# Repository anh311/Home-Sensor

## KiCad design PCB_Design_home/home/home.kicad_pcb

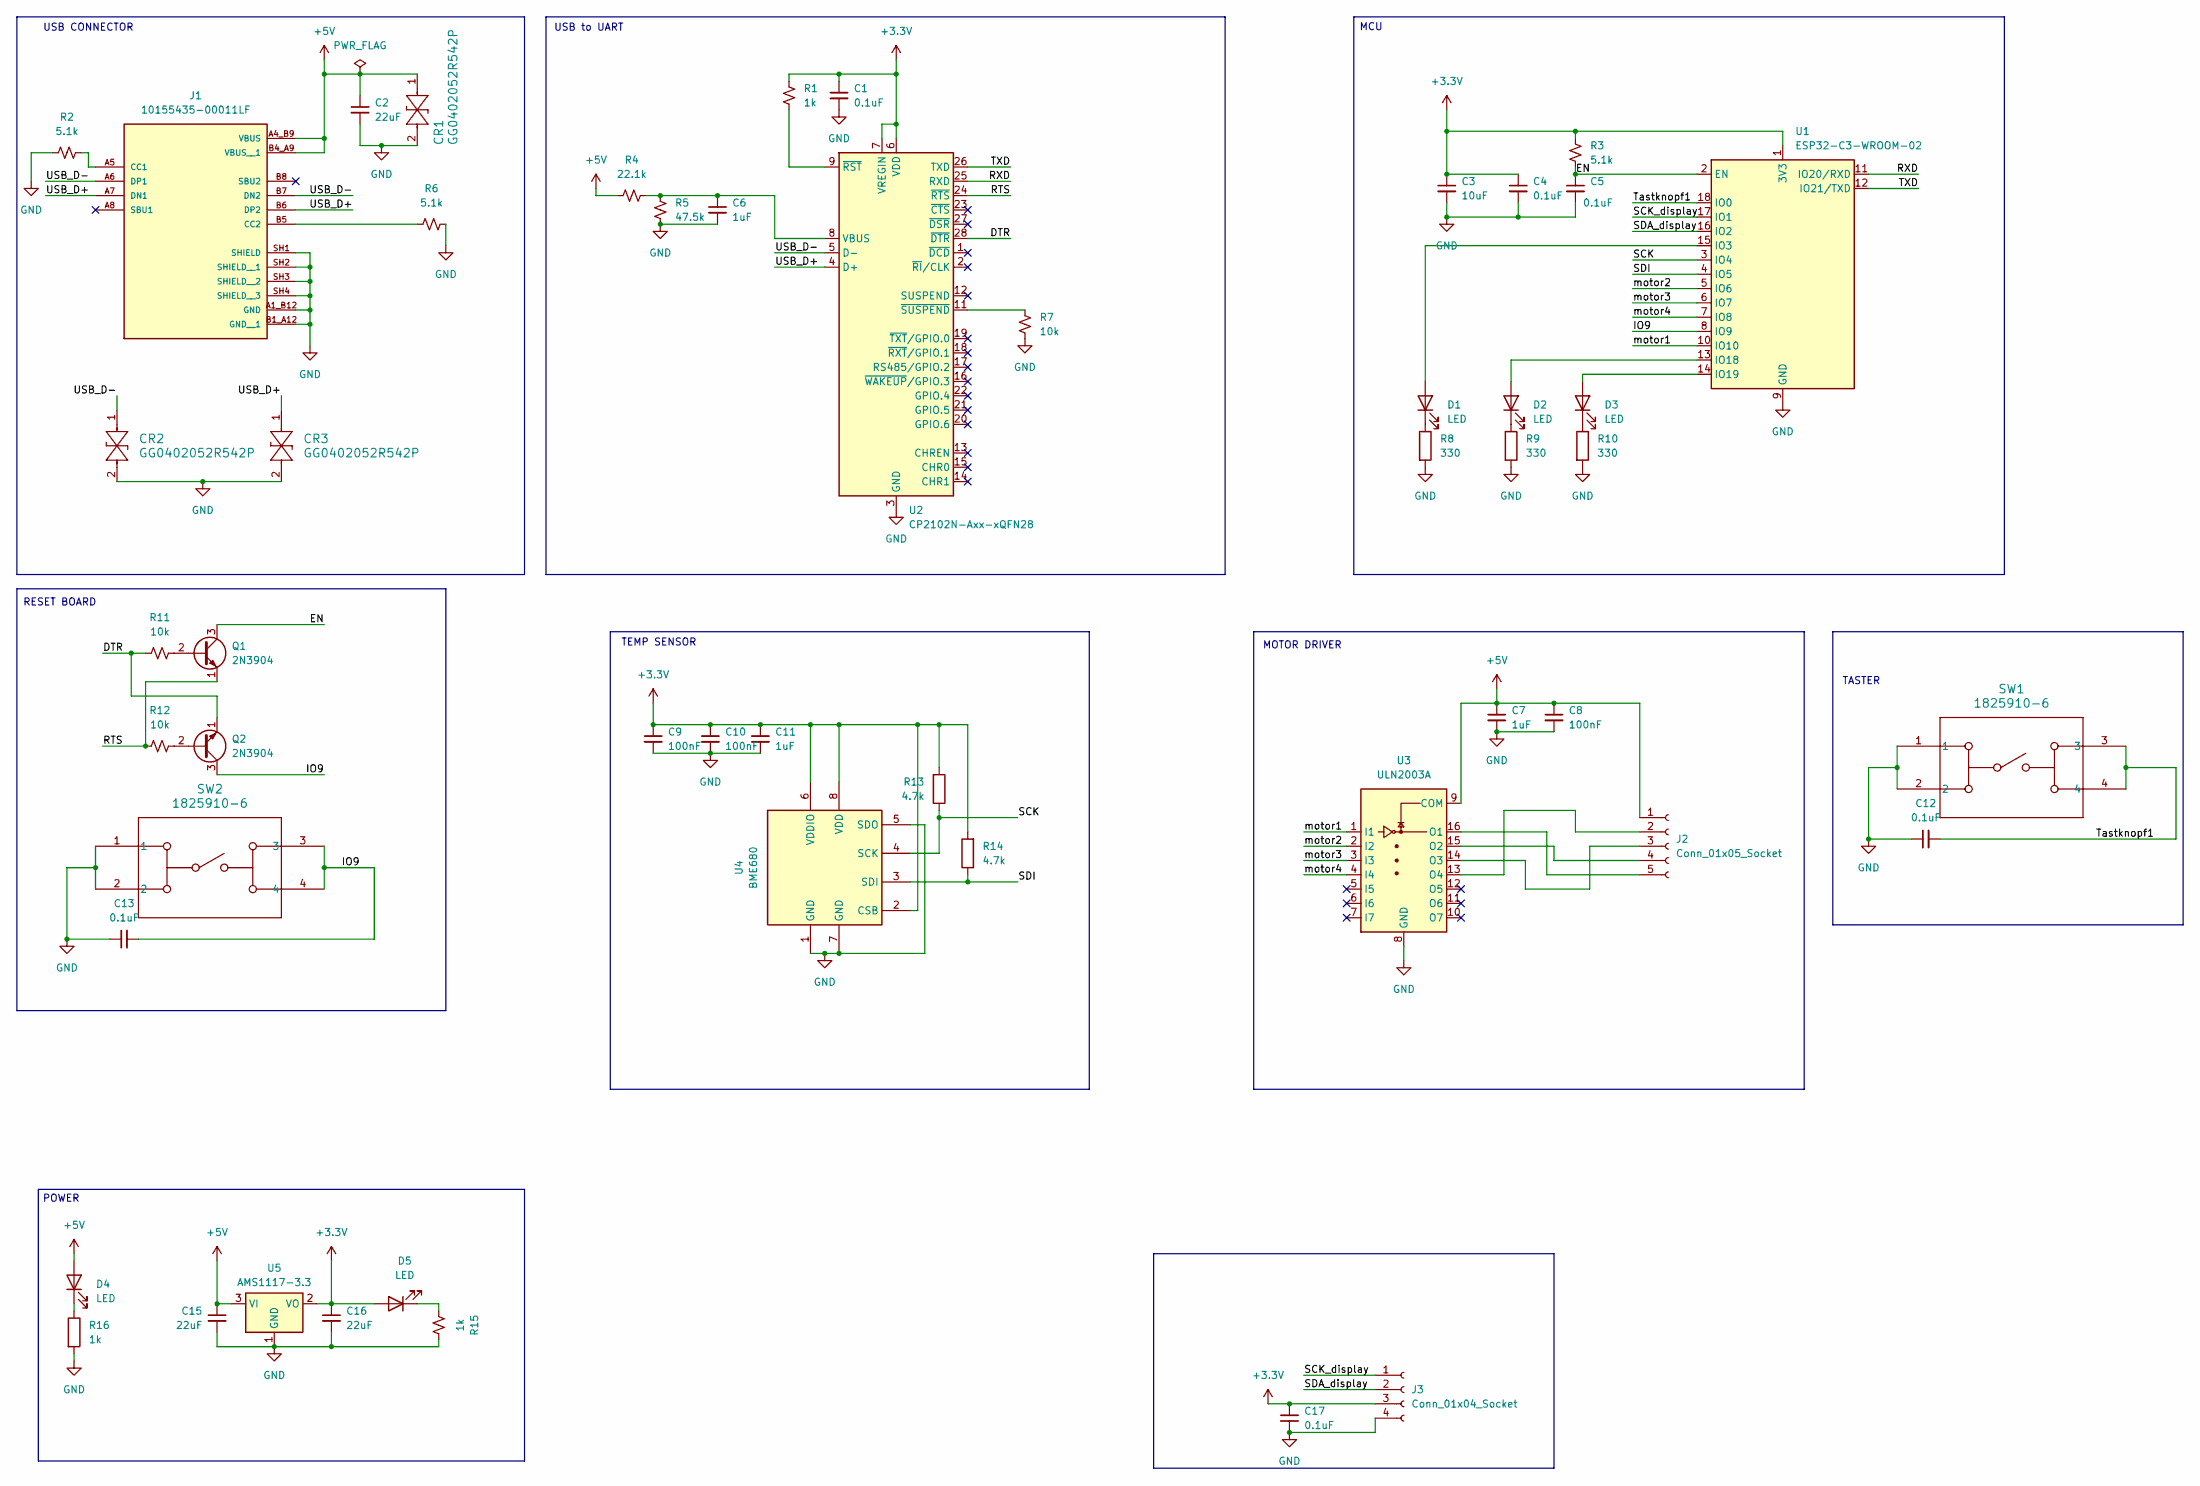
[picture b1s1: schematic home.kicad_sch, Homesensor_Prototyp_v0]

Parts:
C1, C4, C5, C12, C13, C17: 0.1uF; C_0603_1608Metric_Pad1.08x0.95mm_HandSolder
C2, C15, C16: 22uF; C_0603_1608Metric_Pad1.08x0.95mm_HandSolder
C3: 10uF; C_0603_1608Metric_Pad1.08x0.95mm_HandSolder
C6, C7, C11: 1uF; C_0603_1608Metric_Pad1.08x0.95mm_HandSolder
C8, C9, C10: 100nF; C_0603_1608Metric_Pad1.08x0.95mm_HandSolder
CR1, CR2, CR3: GG0402052R542P; TVS_GG0402_KAV
D1, D2, D3, D4, D5: LED; LED_0603_1608Metric_Pad1.05x0.95mm_HandSolder
J1: 10155435-00011LF; AMPHENOL_10155435-00011LF; PARTREV C
J2: Conn_01x05_Socket; PinSocket_1x05_P2.54mm_Vertical
J3: Conn_01x04_Socket; PinSocket_1x04_P2.54mm_Vertical
Q1, Q2: 2N3904; TO-92_Inline
R1, R15, R16: 1k; R_0603_1608Metric_Pad0.98x0.95mm_HandSolder
R2, R3, R6: 5.1k; R_0603_1608Metric_Pad0.98x0.95mm_HandSolder
R4: 22.1k; R_0603_1608Metric_Pad0.98x0.95mm_HandSolder
R5: 47.5k; R_0603_1608Metric_Pad0.98x0.95mm_HandSolder
R7, R11, R12: 10k; R_0603_1608Metric_Pad0.98x0.95mm_HandSolder
R8, R9, R10: 330; R_0603_1608Metric_Pad0.98x0.95mm_HandSolder
R13, R14: 4.7k; R_0603_1608Metric_Pad0.98x0.95mm_HandSolder
SW1, SW2: 1825910-6; SW4_1825910-B_TEC
U1: ESP32-C3-WROOM-02
U2: CP2102N-Axx-xQFN28; QFN50P500X500X80-29N
U3: ULN2003A; DIP-16_STM
U4: BME680; Bosch_LGA-8_3x3mm_P0.8mm_ClockwisePinNumbering
U5: AMS1117-3.3; SOT-223-3_TabPin2

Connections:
+3.3V: C1.1, C3.1, C4.1, C9.1, C10.1, C11.1, C16.1, C17.1, D5.2 (A), J3.3, R1.2, R3.2, R13.2, R14.2, U1.1 (3V3), U2.6 (VDD), U2.7 (VREGIN), U4.2 (CSB), U4.6 (VDDIO), U4.8 (VDD), U5.2 (VO)
+5V: C2.1, C7.1, C8.1, C15.1, CR1.1, D4.2 (A), J1.A4_B9 (VBUS), J1.B4_A9 (VBUS__1), J2.1, R4.2, U3.9 (COM), U5.3 (VI)
/DTR: Q2.1 (E), R11.2, U2.28 (~DTR)
/EN: C5.1, Q1.3 (C), R3.1, U1.2 (EN)
/IO9: C13.2, Q2.3 (C), SW2.3, SW2.4, U1.8 (IO9)
/RTS: Q1.1 (E), R12.1, U2.24 (~RTS)
/RXD: U1.11 (IO20/RXD), U2.25 (RXD)
/SCK: R13.1, U1.3 (IO4), U4.4 (SCK)
/SCK_display: J3.1, U1.17 (IO1)
/SDA_display: J3.2, U1.16 (IO2)
/SDI: R14.1, U1.4 (IO5), U4.3 (SDI)
/TXD: U1.12 (IO21/TXD), U2.26 (TXD)
/Tastknopf1: C12.2, SW1.3, SW1.4, U1.18 (IO0)
/USB_D+: CR3.1, J1.A7 (DN1), J1.B6 (DP2), U2.4 (D+)
/USB_D-: CR2.1, J1.A6 (DP1), J1.B7 (DN2), U2.5 (D-)
/motor1: U1.10 (IO10), U3.1 (I1)
/motor2: U1.5 (IO6), U3.2 (I2)
/motor3: U1.6 (IO7), U3.3 (I3)
/motor4: U1.7 (IO8), U3.4 (I4)
GND: C1.2, C2.2, C3.2, C4.2, C5.2, C6.2, C7.2, C8.2, C9.2, C10.2, C11.2, C12.1, C13.1, C15.2, C16.2, C17.2, CR1.2, CR2.2, CR3.2, J1.A1_B12 (GND), J1.B1_A12 (GND__1), J1.SH1 (SHIELD), J1.SH2 (SHIELD__1), J1.SH3 (SHIELD__2), J1.SH4 (SHIELD__3), J3.4, R2.2, R5.1, R6.1, R7.1, R8.2, R9.2, R10.2, R15.1, R16.2, SW1.1, SW1.2, SW2.1, SW2.2, U1.9 (GND), U1.19 (GND), U2.3 (GND), U2.29 (GND), U3.8 (GND), U4.1 (GND), U4.5 (SDO), U4.7 (GND), U5.1 (GND)
unnamed: D1.2 (A), U1.15 (IO3)
unnamed: D1.1 (K), R8.1
unnamed: D2.2 (A), U1.13 (IO18)
unnamed: D2.1 (K), R9.1
unnamed: D3.2 (A), U1.14 (IO19)
unnamed: D3.1 (K), R10.1
unnamed: D4.1 (K), R16.1
unnamed: D5.1 (K), R15.2
unnamed: J1.A5 (CC1), R2.1
unnamed: J1.B5 (CC2), R6.2
unnamed: J2.2, U3.13 (O4)
unnamed: J2.3, U3.14 (O3)
unnamed: J2.4, U3.15 (O2)
unnamed: J2.5, U3.16 (O1)
unnamed: Q1.2 (B), R11.1
unnamed: Q2.2 (B), R12.2
unnamed: C6.1, R4.1, R5.2, U2.8 (VBUS)
unnamed: R1.1, U2.9 (~RST)
unnamed: R7.2, U2.11 (~SUSPEND)

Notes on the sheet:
POWER
USB to UART
MOTOR DRIVER
TASTER
RESET BOARD
TEMP SENSOR
USB CONNECTOR
MCU

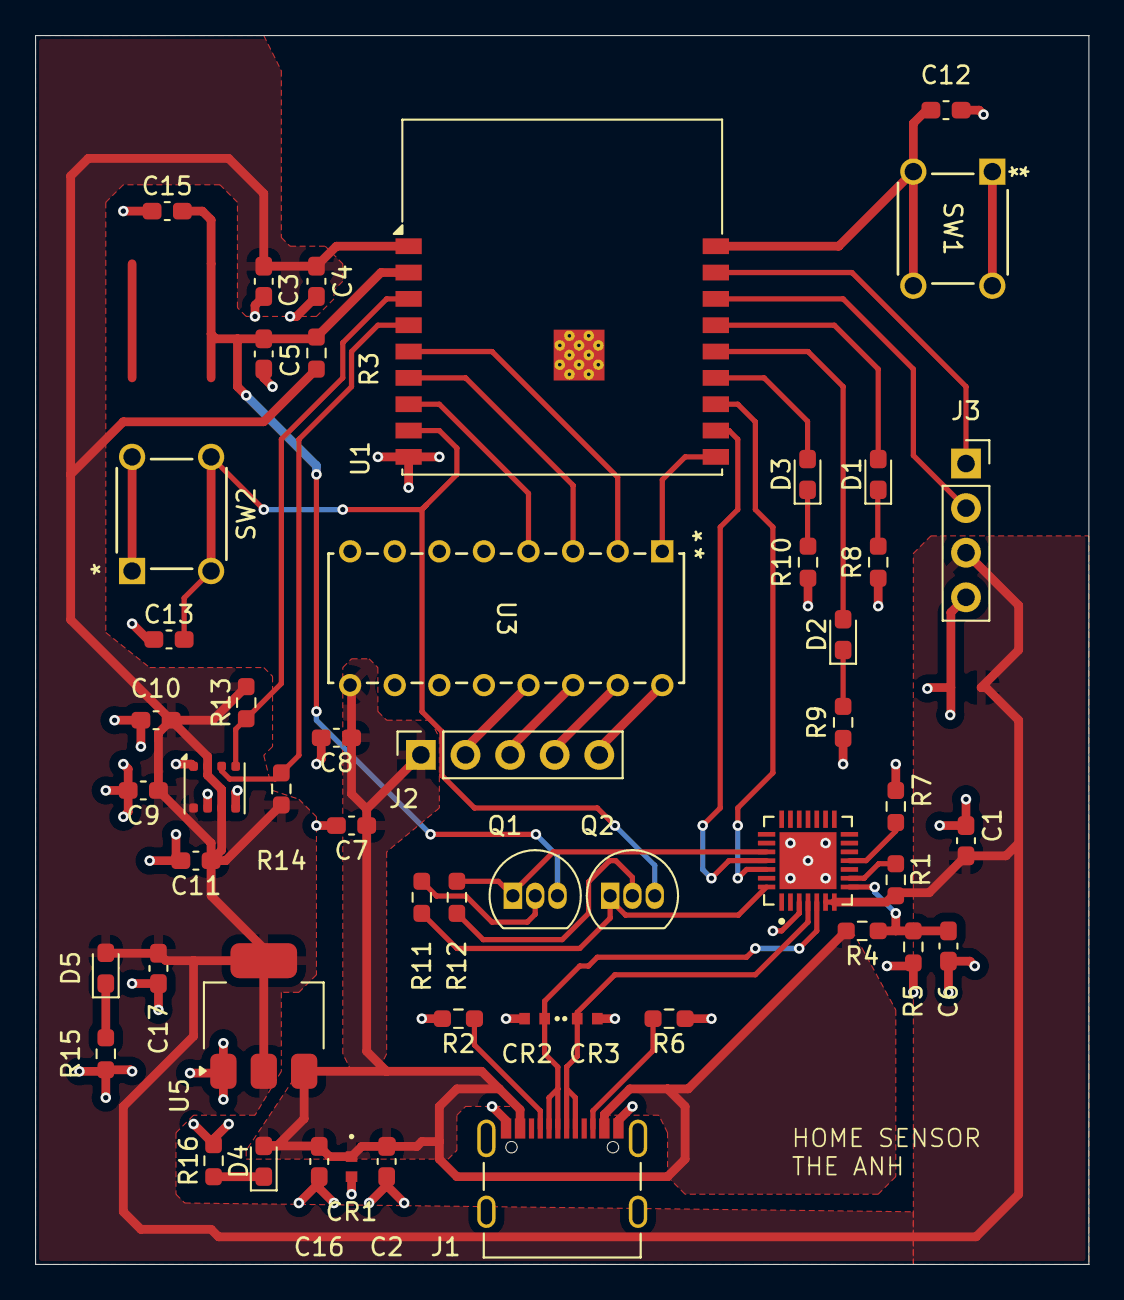
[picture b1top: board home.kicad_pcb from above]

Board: 2 copper layers, 60.0 x 70.0 mm, 52 parts (0 on the bottom side), 39 nets.

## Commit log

2025-12-27 Erster Commit meines HomeSensor-Projekts
2026-01-13 Update Display
2026-01-15 Temporary placement
2026-02-24 Testing
2026-02-26 Testing HW#
2026-02-26 Testing HW
2026-03-01 OLED Test
2026-03-02 BME680 test
